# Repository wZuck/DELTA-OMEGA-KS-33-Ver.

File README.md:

[English](README.md) | [简体中文](README.zh-CN.md)

# DELTA OMEGA KS-33 Ver.

A portable low-profile wireless 3×5+2 split keyboard.

> [!IMPORTANT]
> DELTA OMEGA KS-33 Ver. is a modification of the original DELTA OMEGA design,
> converted to the **Gateron KS-33 Low Profile 3.0 five-pin** switch platform.
> The split wireless architecture and compact 3×5+2 layout are retained. The
> main changes are the KS-33 PCB footprints, matrix routing and validation,
> direct-solder switch installation, KS-33-specific case clearance with a
> raised outer rim, the matching keycap fit envelope, and updated firmware,
> BOM, build, and mechanical documentation. The original Rev4 ULP PCB and
> Gerbers remain available for reference.

## Overview

- Switch support: Gateron KS-33 Low Profile 3.0, five-pin MX PCB layout
- 34 keys, splayed and staggered with 18 × 17 mm key pitch
- Wireless
- CNC aluminum case

## Parameters

## Documentation

> [!NOTE]
> Rev5 is a **five-pin low-profile MX** build. It keeps the compact 18 × 17 mm layout, so keycap footprint must be checked before ordering: standard 19.05 mm-spaced MX keycaps can interfere between rows. The original Rev4 ULP PCB and Gerbers remain in the repository for reference.

- [Getting Started](./docs/GETTING_STARTED.md)
- [Rev5 Mechanical Notes](./docs/MECHANICAL.md)
- [Rev5 Review Summary](./docs/REVIEW_REV5.md)
- [Bill of Materials](./docs/BOM.md)
- [Build Guides](./docs/BUILD_GUIDES.md)
- [Video](https://youtu.be/UktrqN3MlLI)
- [PCB](./pcb/README.md)
- [Case](./case/README.md)
- [Firmware Notes](./firmware/README.md)
- [ZMK Keyboard Module](https://github.com/unspecworks/zmk-keyboard-delta-omega)
- [Pre-conf ZMK Config](https://github.com/unspecworks/zmk-delta-omega)
- Keycaps
  - [Rev5 fit envelope and requirements](./docs/MECHANICAL.md)

## Photos

- [Gallery](./gallery/README.md)
- [Prototype Gallery](./images/README.md)
  - Diff: Port position, Thumb-cluster layout and only hot-plate way.

## Acknowledgments and Inspirations

- [GEIGEIGEIST/TOTEM](https://github.com/GEIGEIGEIST/TOTEM)
- [mikeholscher/zmk-config-mikecinq](https://github.com/mikeholscher/zmk-config-mikecinq)
- [pashutk/Cherry_MX_ULP](https://github.com/pashutk/Cherry_MX_ULP)
- [zmk-rgbled-widget](https://github.com/caksoylar/zmk-rgbled-widget)
- [infused-kim/kb_ergogen_fp](https://github.com/infused-kim/kb_ergogen_fp)
- [ceoloide/ergogen-footprints](https://github.com/ceoloide/ergogen-footprints)
- [kiswitch/kiswitch](https://github.com/kiswitch/kiswitch)

## Limitations and Disclaimer

This is a hobby-driven project. Some aspects may be incomplete, imperfect, or problematic. Use this project **at your own risk**, and note that no warranties or guarantees are provided.

## License

DELTA OMEGA KS-33 Ver. is licensed under [CERN-OHL-W-2.0](./LICENSE.md).

See [NOTICE.md](./NOTICE.md) for the Rev5 modification notice and
[THIRD_PARTY_NOTICES.md](./THIRD_PARTY_NOTICES.md) for third-party components,
licences, names, and source status.

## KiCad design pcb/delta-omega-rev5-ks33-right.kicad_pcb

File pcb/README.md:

[English](README.md) | [简体中文](README.zh-CN.md)

# PCB

> [!TIP]
> If this is your first visit, please read the [Getting Started guide](./../docs/GETTING_STARTED.md) first.

---

## PCB List

| File | Description | Note |
|---|---|---|
| `delta-omega-rev5-ks33-left` | Rev5 left PCB for Gateron KS-33 LP 3.0 five-pin | Current version |
| `delta-omega-rev5-ks33-right` | Rev5 right PCB for Gateron KS-33 LP 3.0 five-pin | Current version |
| `delta-omega-rev5-ks33-both` | Rev5 left and right PCB with mouse-bite connection | Check panel separation before use |
| `delta-omega-rev4-handsolder-both` | Original ULP left and right PCB with mouse-bite connection | Legacy, not tested |
| `delta-omega-rev4-handsolder-left` | Original ULP left PCB | Legacy |
| `delta-omega-rev4-handsolder-right` | Original ULP right PCB | Legacy |
| `delta_omega_bottom_cover` | Bottom cover PCB plate | Reversible |
| `delta-omega-rev4-smd-both` | Original ULP SMD version | Legacy, not tested |

Rev5 uses a custom `Gateron_KS33_LP_3.0_5Pin` footprint:

- Standard MX electrical-pin positions
- 5.0 mm center hole
- 1.70 mm locator holes at ±5.08 mm
- Separate SOD-323 diode position outside the switch body

## Rev5 Verification

- KiCad DRC: 0 violations and 0 unconnected items for left, right, and panel
- 34 switches and 34 SOD-323 diodes total
- Two-layer 1.6 mm PCB, 0.2 mm minimum signal track width
- 0.2 mm copper-to-edge clearance outside the XIAO castellations
- XIAO edge-pad exception is scoped by the project `.kicad_dru` file
- Split ground-zone islands are connected with explicit tracks
- Gerbers, drill files, drill maps, and ZIP archives were regenerated from the
  checked-in Rev5 boards

The project has no KiCad schematic, so verification covers PCB connectivity,
matrix mapping, diode orientation, copper rules, and fabrication outputs rather
than schematic-to-PCB parity.

---

## How to Order

This guide is written based on **[JLCPCB](https://jlcpcb.com)**. While other PCB manufacturers may differ slightly, most ordering steps are very similar.

To place an order, upload the matching ZIP from [./gerbers/](./gerbers/).
For the current switch scheme, use the `rev5-ks33` archives.

---

### Recommended Options

| Specification     | Recommended                          | Notes                                                                 |
|-------------------|--------------------------------------|----------------------------------------------------------------------|
| Base Material     | FR-4                                 | Standard PCB substrate material                                      |
| Layers            | 2                                    | Two-layer board                                                      |
| PCB Quantity      | As many as needed                    |                                                                      |
| Product Type      | Industrial / Consumer Electronics    |                                                                      |
| Different Designs | 1                                    | If uploading a combined left & right PCB Gerber, select **2**.[^1]   |
| PCB Thickness     | 1.6 mm                               | Required for the 1.2 mm KS-33 locator pegs and 3.0 mm pins              |
| PCB Color         | Your preference                      |                                                                      |
| Surface Finish    | Your preference                      |                                                                      |
| Mark on PCB       | Remove Mark                          | Recommended for a cleaner finish                                     |

[^1]: If not selected, JLCPCB will automatically review your order and guide you to the correct option.

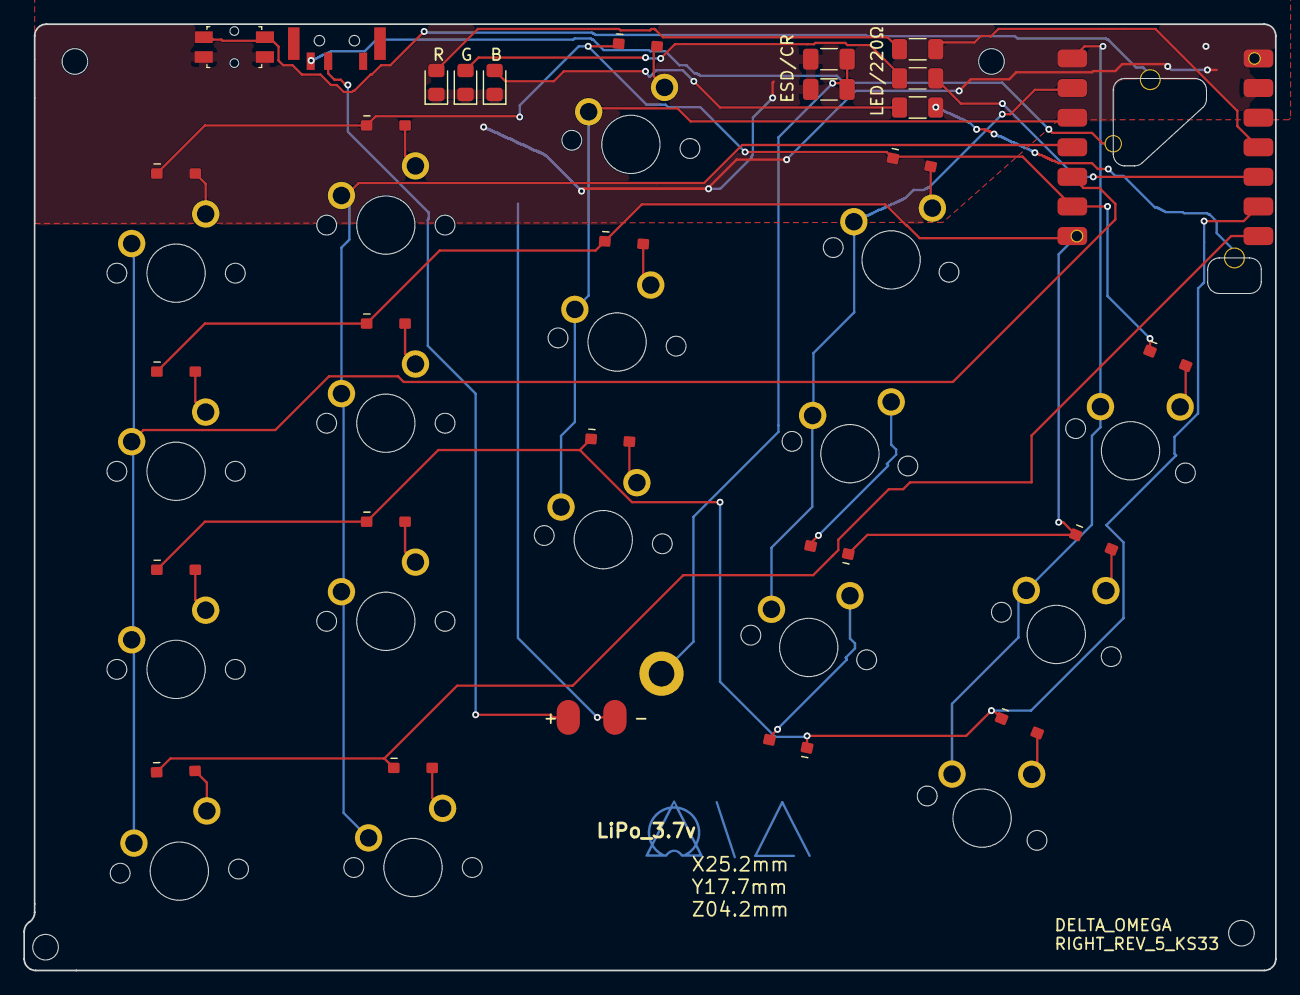
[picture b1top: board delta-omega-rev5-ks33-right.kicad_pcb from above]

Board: 2 copper layers, 107.4 x 81.2 mm, 50 parts (0 on the bottom side), 35 nets.

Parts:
C1: C_1206_3216Metric_Pad1.33x1.80mm_HandSolder
D18, D19, D20, D21, D22, D23, D24, D25, D26, D27, D28, D29, D30, D31, D32, D33, D34: 1N4148WS
H2: (no value)
L1, L2, L3: LED_0805_2012Metric_Pad1.15x1.40mm_HandSolder
MCU1: XIAO-nRF52840-SMD
MH2, MH4, MH6, MH8: (no value)
R1, R2, R3: R_1206_3216Metric_Pad1.30x1.75mm_HandSolder
R1#2: C_1206_3216Metric_Pad1.33x1.80mm_HandSolder
RST2: (no value)
SW18, SW19, SW20, SW21, SW22, SW23, SW24, SW25, SW26, SW27, SW28, SW29, SW30, SW31, SW32, SW33, SW34: KS33_LP_3.0_5Pin
TH2: (no value)

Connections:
R_C1: MCU1.1, SW18.1, SW19.1, SW20.1
R_C2: MCU1.2, SW21.1, SW22.1, SW23.1
R_C3: MCU1.3, SW24.1, SW25.1, SW26.1
R_C4: MCU1.4, SW27.1, SW28.1, SW29.1, SW33.1
R_C5: MCU1.5, SW30.1, SW31.1, SW32.1, SW34.1
R_CGND: C1.2, R1#2.2
R_GND: C1.1, L1.1, L2.1, L3.1, MCU1.13, R1#2.1, RST2.2, RST2.4, TH2.1
R_LED1: L1.2, R1.1
R_LED2: L2.2, R2.1
R_LED3: L3.2, R3.1
R_LED_R1: MCU1.11, R1.2
R_LED_R2: MCU1.10, R2.2
R_LED_R3: MCU1.17, R3.2
R_R1: D20.1, D23.1, D26.1, D29.1, D32.1, MCU1.6
R_R2: D19.1, D22.1, D25.1, D28.1, D31.1, MCU1.7
R_R3: D18.1, D21.1, D24.1, D27.1, D30.1, MCU1.9
R_R4: D33.1, D34.1, MCU1.8
R_RST: MCU1.21, RST2.1, RST2.3
SW18_1: D18.2, SW18.2
SW19_1: D19.2, SW19.2
SW20_1: D20.2, SW20.2
SW21_1: D21.2, SW21.2
SW22_1: D22.2, SW22.2
SW23_1: D23.2, SW23.2
SW24_1: D24.2, SW24.2
SW25_1: D25.2, SW25.2
SW26_1: D26.2, SW26.2
SW27_1: D27.2, SW27.2
SW28_1: D28.2, SW28.2
SW29_1: D29.2, SW29.2
SW30_1: D30.2, SW30.2
SW31_1: D31.2, SW31.2
SW32_1: D32.2, SW32.2
SW33_1: D33.2, SW33.2
SW34_1: D34.2, SW34.2

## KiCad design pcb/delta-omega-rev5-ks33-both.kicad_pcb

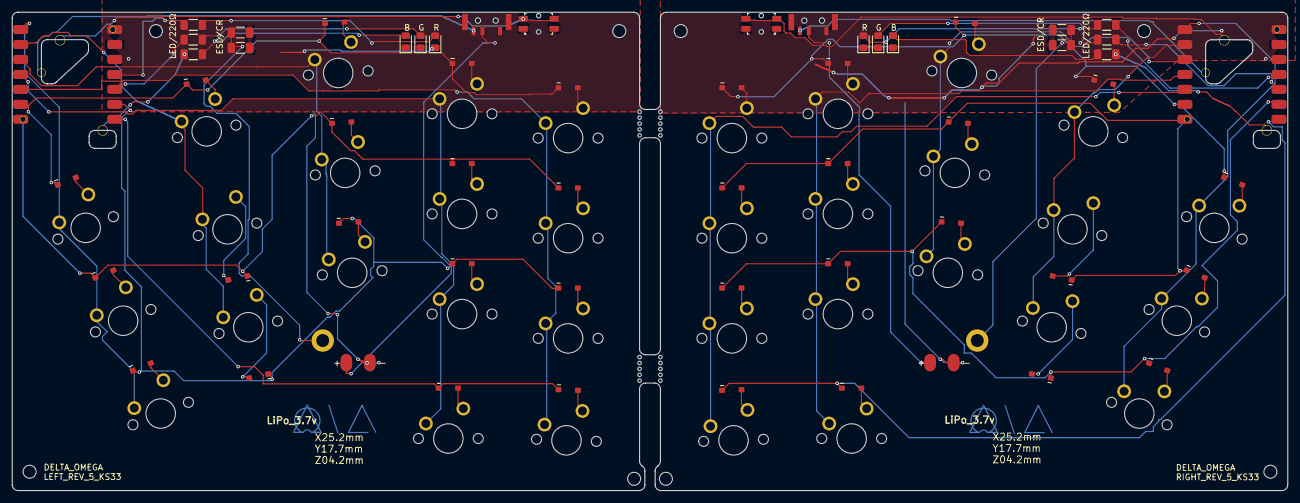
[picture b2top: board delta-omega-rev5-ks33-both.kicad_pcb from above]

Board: 2 copper layers, 216.5 x 81.2 mm, 100 parts (0 on the bottom side), 70 nets.

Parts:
C1, C1#2: C_1206_3216Metric_Pad1.33x1.80mm_HandSolder
D1, D2, D3, D4, D5, D6, D7, D8, D9, D10, D11, D12, D13, D14, D15, D16, D17, D18, D19, D20, D21, D22, D23, D24, D25, D26, D27, D28, D29, D30, D31, D32, D33, D34: 1N4148WS
H1, H2: (no value)
L1, L1#2, L2, L2#2, L3, L3#2: LED_0805_2012Metric_Pad1.15x1.40mm_HandSolder
MCU1, MCU2: XIAO-nRF52840-SMD
MH1, MH2, MH3, MH4, MH5, MH6, MH7, MH8: (no value)
R1, R1#3, R2, R2#2, R3, R3#2: R_1206_3216Metric_Pad1.30x1.75mm_HandSolder
R1#2, R1#4: C_1206_3216Metric_Pad1.33x1.80mm_HandSolder
RST1, RST2: (no value)
SW1, SW2, SW3, SW4, SW5, SW6, SW7, SW8, SW9, SW10, SW11, SW12, SW13, SW14, SW15, SW16, SW17, SW18, SW19, SW20, SW21, SW22, SW23, SW24, SW25, SW26, SW27, SW28, SW29, SW30, SW31, SW32, SW33, SW34: KS33_LP_3.0_5Pin
TH1, TH2: (no value)

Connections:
L_C1: MCU2.1, SW1.1, SW2.1, SW3.1
L_C2: MCU2.2, SW4.1, SW5.1, SW6.1
L_C3: MCU2.3, SW7.1, SW8.1, SW9.1
L_C4: MCU2.4, SW10.1, SW11.1, SW12.1, SW16.1
L_C5: MCU2.5, SW13.1, SW14.1, SW15.1, SW17.1
L_CGND: C1#2.1, R1#2.1
L_GND: C1#2.2, L1.1, L2#2.1, L3#2.1, MCU2.13, R1#2.2, RST1.2, RST1.4, TH1.1
L_LED1: L1.2, R1#3.2
L_LED2: L2#2.2, R2#2.2
L_LED3: L3#2.2, R3#2.2
L_LED_R1: MCU2.11, R1#3.1
L_LED_R2: MCU2.10, R2#2.1
L_LED_R3: MCU2.17, R3#2.1
L_R1: D3.1, D6.1, D9.1, D12.1, D15.1, MCU2.6
L_R2: D2.1, D5.1, D8.1, D11.1, D14.1, MCU2.7
L_R3: D1.1, D4.1, D7.1, D10.1, D13.1, MCU2.9
L_R4: D16.1, D17.1, MCU2.8
L_RST: MCU2.21, RST1.1, RST1.3
R_C1: MCU1.1, SW18.1, SW19.1, SW20.1
R_C2: MCU1.2, SW21.1, SW22.1, SW23.1
R_C3: MCU1.3, SW24.1, SW25.1, SW26.1
R_C4: MCU1.4, SW27.1, SW28.1, SW29.1, SW33.1
R_C5: MCU1.5, SW30.1, SW31.1, SW32.1, SW34.1
R_CGND: C1.2, R1#4.2
R_GND: C1.1, L1#2.1, L2.1, L3.1, MCU1.13, R1#4.1, RST2.2, RST2.4, TH2.1
R_LED1: L1#2.2, R1.1
R_LED2: L2.2, R2.1
R_LED3: L3.2, R3.1
R_LED_R1: MCU1.11, R1.2
R_LED_R2: MCU1.10, R2.2
R_LED_R3: MCU1.17, R3.2
R_R1: D20.1, D23.1, D26.1, D29.1, D32.1, MCU1.6
R_R2: D19.1, D22.1, D25.1, D28.1, D31.1, MCU1.7
R_R3: D18.1, D21.1, D24.1, D27.1, D30.1, MCU1.9
R_R4: D33.1, D34.1, MCU1.8
R_RST: MCU1.21, RST2.1, RST2.3
SW1_1: D1.2, SW1.2
SW2_1: D2.2, SW2.2
SW3_1: D3.2, SW3.2
SW4_1: D4.2, SW4.2
SW5_1: D5.2, SW5.2
SW6_1: D6.2, SW6.2
SW7_1: D7.2, SW7.2
SW8_1: D8.2, SW8.2
SW9_1: D9.2, SW9.2
SW10_1: D10.2, SW10.2
SW11_1: D11.2, SW11.2
SW12_1: D12.2, SW12.2
SW13_1: D13.2, SW13.2
SW14_1: D14.2, SW14.2
SW15_1: D15.2, SW15.2
SW16_1: D16.2, SW16.2
SW17_1: D17.2, SW17.2
SW18_1: D18.2, SW18.2
SW19_1: D19.2, SW19.2
SW20_1: D20.2, SW20.2
SW21_1: D21.2, SW21.2
SW22_1: D22.2, SW22.2
SW23_1: D23.2, SW23.2
SW24_1: D24.2, SW24.2
SW25_1: D25.2, SW25.2
SW26_1: D26.2, SW26.2
SW27_1: D27.2, SW27.2
SW28_1: D28.2, SW28.2
SW29_1: D29.2, SW29.2
SW30_1: D30.2, SW30.2
SW31_1: D31.2, SW31.2
SW32_1: D32.2, SW32.2
SW33_1: D33.2, SW33.2
SW34_1: D34.2, SW34.2
